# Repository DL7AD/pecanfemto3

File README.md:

# Pecan Femto 3

This is a small APRS tracker which has been made especially for balloon tracking. When designing this PCB we took into account to get a small PCB with basic tracking functions with less features. This PCB has been designed after we build Pecan Pico 6 and we did some changes compared to the last one.

- We took a NXP LPC824 microcontroller insteas of the LPC1114. It has a pin switch matrix, which basically means that almost every pin can be taken for every function.
- We took a much smaller TCXO.
- We left the parts for TCXO modulation.
- The uBlox MAX7C has been replaced by an uBlox EVA7M module which is basically a smaller and lighter GPS receiver.
- Added a Step-Down regulator in the power management in order to make the use of LiPO's available.
- We removed the ability to receive for this tracker.
- The GPS is switched by the microcontroller.

Like the Pecan Pico 6, this PCB is also solar enabled. So the tracker could stay almost alive forever.

Versions
========
- Pecan Femto 3a can be found in [branch master](https://github.com/DL7AD/pecanfemto3/tree/master) !!! CONTAINS ERRORS
- Pecan Femto 3b can be found in [branch 3b](https://github.com/DL7AD/pecanfemto3/tree/3b)

PCB errors
==========
At version 3a, we've done some errors on the PCB:

- The TCXO pins are flipped
- There's an pullup resistor missing at RADIO_SDN (because it's connected to a pin a the microcontroller, which has no internal pullup capability)

Version 3b sould actually have no errors but we've never tested it.

Disadvantages and concept errors
================================

Since we use a different microcontroller, we did not take into account, that there's a different ISP entry pin for the LPC824. The ISP entry pin is located at pin PIO0_12 which we've used as GPS power pin. The problem is, that the tracker doesn't startup automatically, because the GPS power pin is held low by the GPS itself, so the microcontroller starts in ISP mode. There's only one solution for it: Enabling the CRP3 mode. Enabling CRP3 disables the ISP entry pin but it also lockes you out and you are not able to flash the chip anymore.

The PCB ro software also has a bug. Once the PCB is cooled down to -10°C, the modulation somehow changes and so far I couldn't find out, what the error is. The software for this Tracker can be found [here](https://github.com/DL7AD/pecan-lpc82x)

Software
========

Software can be found here: [pecan-lpc82x](https://github.com/DL7AD/pecan-lpc82x)

License
=======
CC-BY-SA 4.0

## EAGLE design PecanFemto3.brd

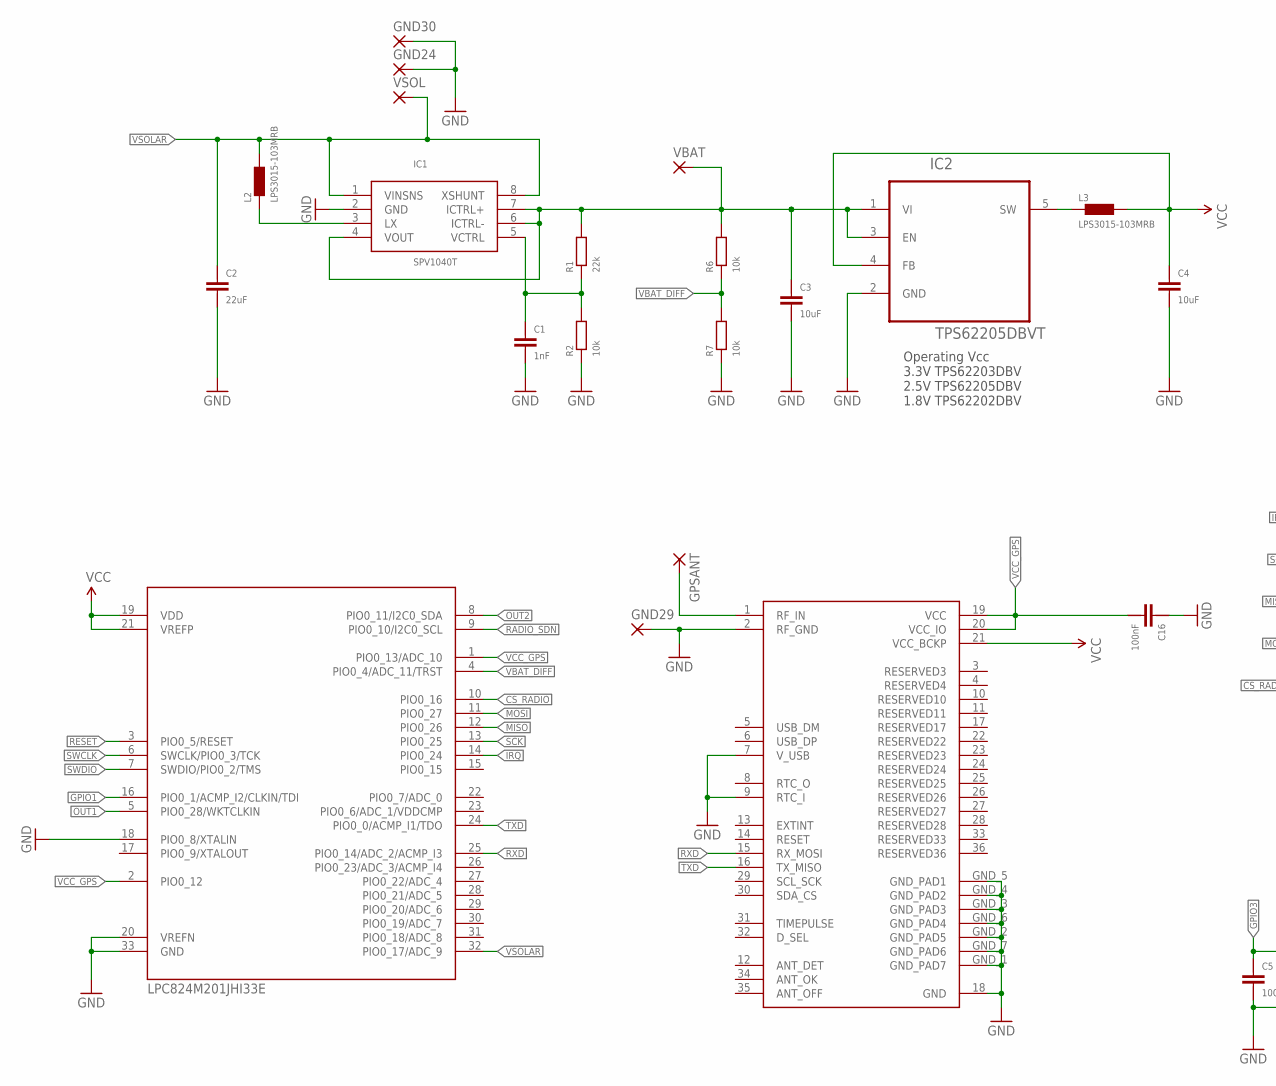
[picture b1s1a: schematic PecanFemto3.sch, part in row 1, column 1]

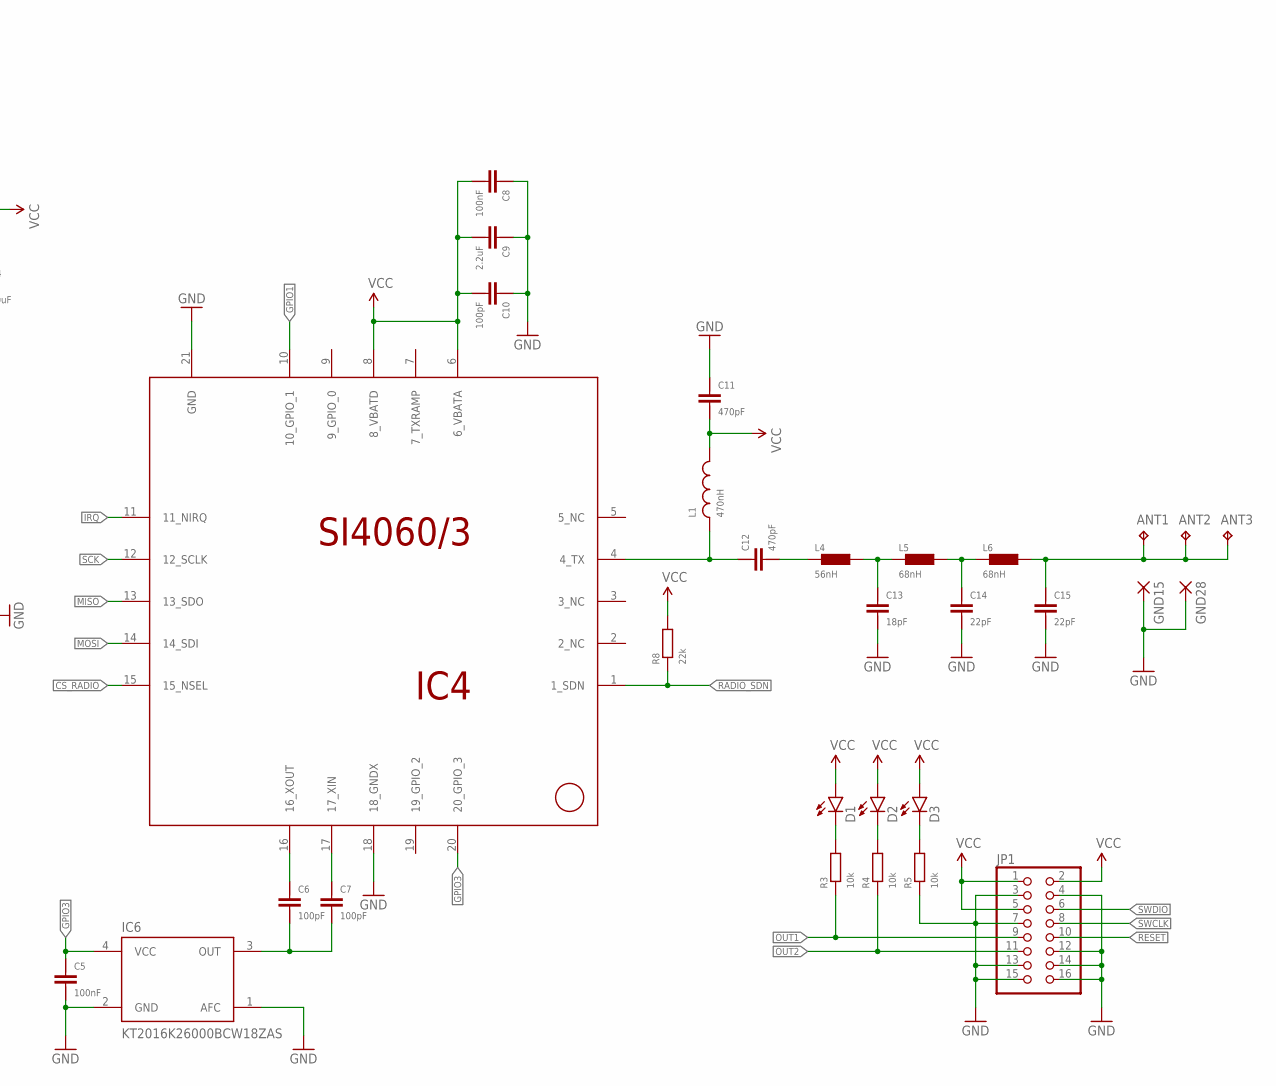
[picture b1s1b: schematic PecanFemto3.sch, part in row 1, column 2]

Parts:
ANT1, ANT2, ANT3: TP; P1-7; MPN ERJ-3EKF62R0V
C1: 1nF; 0402
C2: 22uF; 0805
C3, C4: 10uF; 0805
C5, C8, C16: 100nF; 0402
C6, C7, C10: 100pF; 0402
C9: 2.2uF; 0402
C11, C12: 470pF; 0402
C13: 18pF; 0402
C14, C15: 22pF; 0402
D1, D2, D3: LED0603; LED-0603
GND15, GND24, GND28, GND29, GND30: SMD2; SMD1,27-2,54
GPSANT: SMD2; SMD1,27-2,54
IC1: SPV1040T; TSSOP8
IC2: TPS62205DBVT; SOT95P280X145-5N
IC3: EVA7M
IC4: SI4060/3; QFN-20
IC5: LPC824M201JHI33E; QFN65P500X500X100-33N
IC6: KT2016K26000BCW18ZAS; TCXO_2.0X1.6
JP1: PINHD-2X8; 2X08
L1: 470nH; 0805
L2, L3: LPS3015-103MRB; LPS3015
L4: 56nH; 0402
L5, L6: 68nH; 0402
R1, R8: 22k; 0402
R2, R3, R4, R5, R6, R7: 10k; 0402
VBAT: SMD2; SMD1,27-2,54
VSOL: SMD2; SMD1,27-2,54

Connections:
C12: C12.P$1 (1), L4.P$1 (1)
CS_RADIO: IC4.15 (15_NSEL), IC5.10 (PIO0_16)
GND: C1.P$1 (1), C2.P$1 (1), C3.P$1 (1), C4.P$1 (1), C5.P$1 (1), C8.P$2 (2), C9.P$2 (2), C10.P$2 (2), C11.P$2 (2), C13.P$1 (1), C14.P$1 (1), C15.P$1 (1), C16.P$2 (2), GND15.1, GND24.1, GND28.1, GND29.1, GND30.1, IC1.2 (GND), IC2.2 (GND), IC3.2 (RF_GND), IC3.7 (V_USB), IC3.9 (RTC_I), IC3.18 (GND), IC3.GND_1 (GND_PAD7), IC3.GND_2 (GND_PAD5), IC3.GND_3 (GND_PAD3), IC3.GND_4 (GND_PAD2), IC3.GND_5 (GND_PAD1), IC3.GND_6 (GND_PAD4), IC3.GND_7 (GND_PAD6), IC4.18 (18_GNDX), IC4.21 (GND), IC5.18 (PIO0_8/XTALIN), IC5.20 (VREFN), IC5.33 (GND), IC6.1 (AFC), IC6.2 (GND), JP1.3, JP1.4, JP1.7, JP1.12, JP1.13, JP1.14, JP1.15, JP1.16, R2.P$1 (1), R5.P$1 (1), R7.P$1 (1)
GPIO1: IC4.10 (10_GPIO_1), IC5.16 (PIO0_1/ACMP_I2/CLKIN/TDI)
GPIO3: C5.P$2 (2), IC4.20 (20_GPIO_3), IC6.4 (VCC)
IRQ: IC4.11 (11_NIRQ), IC5.14 (PIO0_24)
L5: C13.P$2 (2), L4.P$2 (2), L5.P$1 (1)
MISO: IC4.13 (13_SDO), IC5.12 (PIO0_26)
MOSI: IC4.14 (14_SDI), IC5.11 (PIO0_27)
unnamed: GPSANT.1, IC3.1 (RF_IN)
unnamed: C12.P$2 (2), IC4.4 (4_TX), L1.1
unnamed: ANT1.TP, ANT2.TP, ANT3.TP, C15.P$2 (2), L6.P$2 (2)
unnamed: C14.P$2 (2), L5.P$2 (2), L6.P$1 (1)
unnamed: C7.P$2 (2), IC4.17 (17_XIN)
unnamed: D1.C, R3.P$2 (2)
unnamed: C6.P$1 (1), C7.P$1 (1), IC6.3 (OUT)
unnamed: C6.P$2 (2), IC4.16 (16_XOUT)
unnamed: D2.C, R4.P$2 (2)
unnamed: D3.C, R5.P$2 (2)
unnamed: IC1.3 (LX), L2.1_1 (1), L2.1_2 (1), L2.1_3 (1), L2.1_4 (1), L2.1_5 (1), L2.1_6 (1), L2.1_7 (1), L2.1_8 (1), L2.1_9 (1)
unnamed: IC2.5 (SW), L3.1_1 (1), L3.1_2 (1), L3.1_3 (1), L3.1_4 (1), L3.1_5 (1), L3.1_6 (1), L3.1_7 (1), L3.1_8 (1), L3.1_9 (1)
unnamed: C1.P$2 (2), IC1.5 (VCTRL), R1.P$1 (1), R2.P$2 (2)
OUT1: IC5.5 (PIO0_28/WKTCLKIN), JP1.9, R3.P$1 (1)
OUT2: IC5.8 (PIO0_11/I2C0_SDA), JP1.11, R4.P$1 (1)
RADIO_SDN: IC4.1 (1_SDN), IC5.9 (PIO0_10/I2C0_SCL), R8.P$1 (1)
RESET: IC5.3 (PIO0_5/RESET), JP1.10
RXD: IC3.15 (RX_MOSI), IC5.25 (PIO0_14/ADC_2/ACMP_I3)
SCK: IC4.12 (12_SCLK), IC5.13 (PIO0_25)
SWCLK: IC5.6 (SWCLK/PIO0_3/TCK), JP1.8
SWDIO: IC5.7 (SWDIO/PIO0_2/TMS), JP1.6
TXD: IC3.16 (TX_MISO), IC5.24 (PIO0_0/ACMP_I1/TDO)
VBAT: C3.P$2 (2), IC1.4 (VOUT), IC1.6 (ICTRL-), IC1.7 (ICTRL+), IC2.1 (VI), IC2.3 (EN), R1.P$2 (2), R6.P$2 (2), VBAT.1
VBAT_DIFF: IC5.4 (PIO0_4/ADC_11/TRST), R6.P$1 (1), R7.P$2 (2)
VCC: C4.P$2 (2), C8.P$1 (1), C9.P$1 (1), C10.P$1 (1), C11.P$1 (1), D1.A, D2.A, D3.A, IC2.4 (FB), IC3.21 (VCC_BCKP), IC4.6 (6_VBATA), IC4.8 (8_VBATD), IC5.19 (VDD), IC5.21 (VREFP), JP1.1, JP1.2, JP1.5, L1.2, L3.2_1 (2), L3.2_2 (2), L3.2_3 (2), L3.2_4 (2), L3.2_5 (2), L3.2_6 (2), L3.2_7 (2), L3.2_8 (2), L3.2_9 (2), R8.P$2 (2)
VCC_GPS: C16.P$1 (1), IC3.19 (VCC), IC3.20 (VCC_IO), IC5.1 (PIO0_13/ADC_10), IC5.2 (PIO0_12)
VSOLAR: C2.P$2 (2), IC1.1 (VINSNS), IC1.8 (XSHUNT), IC5.32 (PIO0_17/ADC_9), L2.2_1 (2), L2.2_2 (2), L2.2_3 (2), L2.2_4 (2), L2.2_5 (2), L2.2_6 (2), L2.2_7 (2), L2.2_8 (2), L2.2_9 (2), VSOL.1

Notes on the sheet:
Operating Vcc 3.3V TPS62203DBV 2.5V TPS62205DBV 1.8V TPS62202DBV

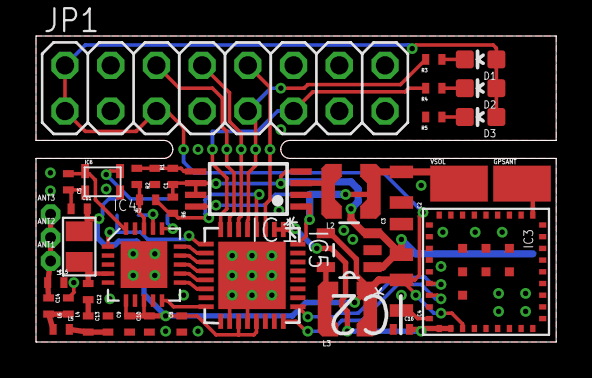
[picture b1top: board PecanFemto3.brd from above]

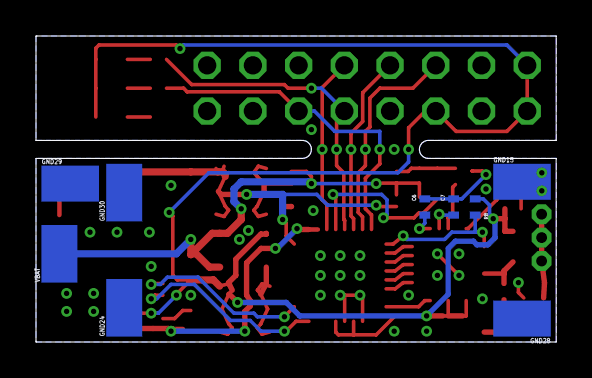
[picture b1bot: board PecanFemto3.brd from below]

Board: 2 copper layers, 28.9 x 17.0 mm, 51 parts (9 on the bottom side), 36 nets.

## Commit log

2015-07-21 Added step down converter
2015-07-23 Moved components around
2015-07-24 Moved parts around
2015-07-27 Moved parts around, added MOSFET switch for GPS
2015-08-05 Moved all parts around
2015-08-11 Removed GPS-Switch-MOSFET and connected parts
2015-08-11 Routed parts
2015-08-13 Updated libraries, moved parts around, routed
2015-08-13 Connected GND
2015-08-13 Moved parts, updated libs, added pads, added programmer pins
2015-08-13 Added via
2015-08-13 Moved via
2015-08-26 Added LEDs, changed size of pinheader, moved parts
2015-08-27 Connected TCXO VCC to Si4464
2015-08-27 Connected V_USB and RTC_I to GND
2015-08-29 Added Gerber files for hackvana
2015-09-01 Moved parts around, updated GERBERs
2015-09-03 Changed naming of parts
2015-09-27 Moved parts in schematic, added PNG files
2015-10-22 Changed part values
2015-10-22 Fixed PecanPico3 errors Removed paste from large pads Added pullup to RADIO_SDN Fixed TCXO swapping (pins inverted) Updated Designators (on silkscreen layer)
2015-10-22 Removed old gerber and picture exports
2015-10-22 Changed TCXO designator, improved EVA7M package
2015-12-19 Added some infos

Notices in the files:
parts and their libraries:
SparkFun-LED: Licensing: Creative Commons ShareAlike 4.0 International - https://creativecommons.org/licenses/by-sa/4.0
